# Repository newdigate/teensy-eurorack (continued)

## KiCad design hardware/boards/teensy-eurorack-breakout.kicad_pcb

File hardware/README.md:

# schematics, printed circuit boards, and panels
* schematic and circuit board files for both boards [here](boards)
* panel designs [here](panel)

# circuits images

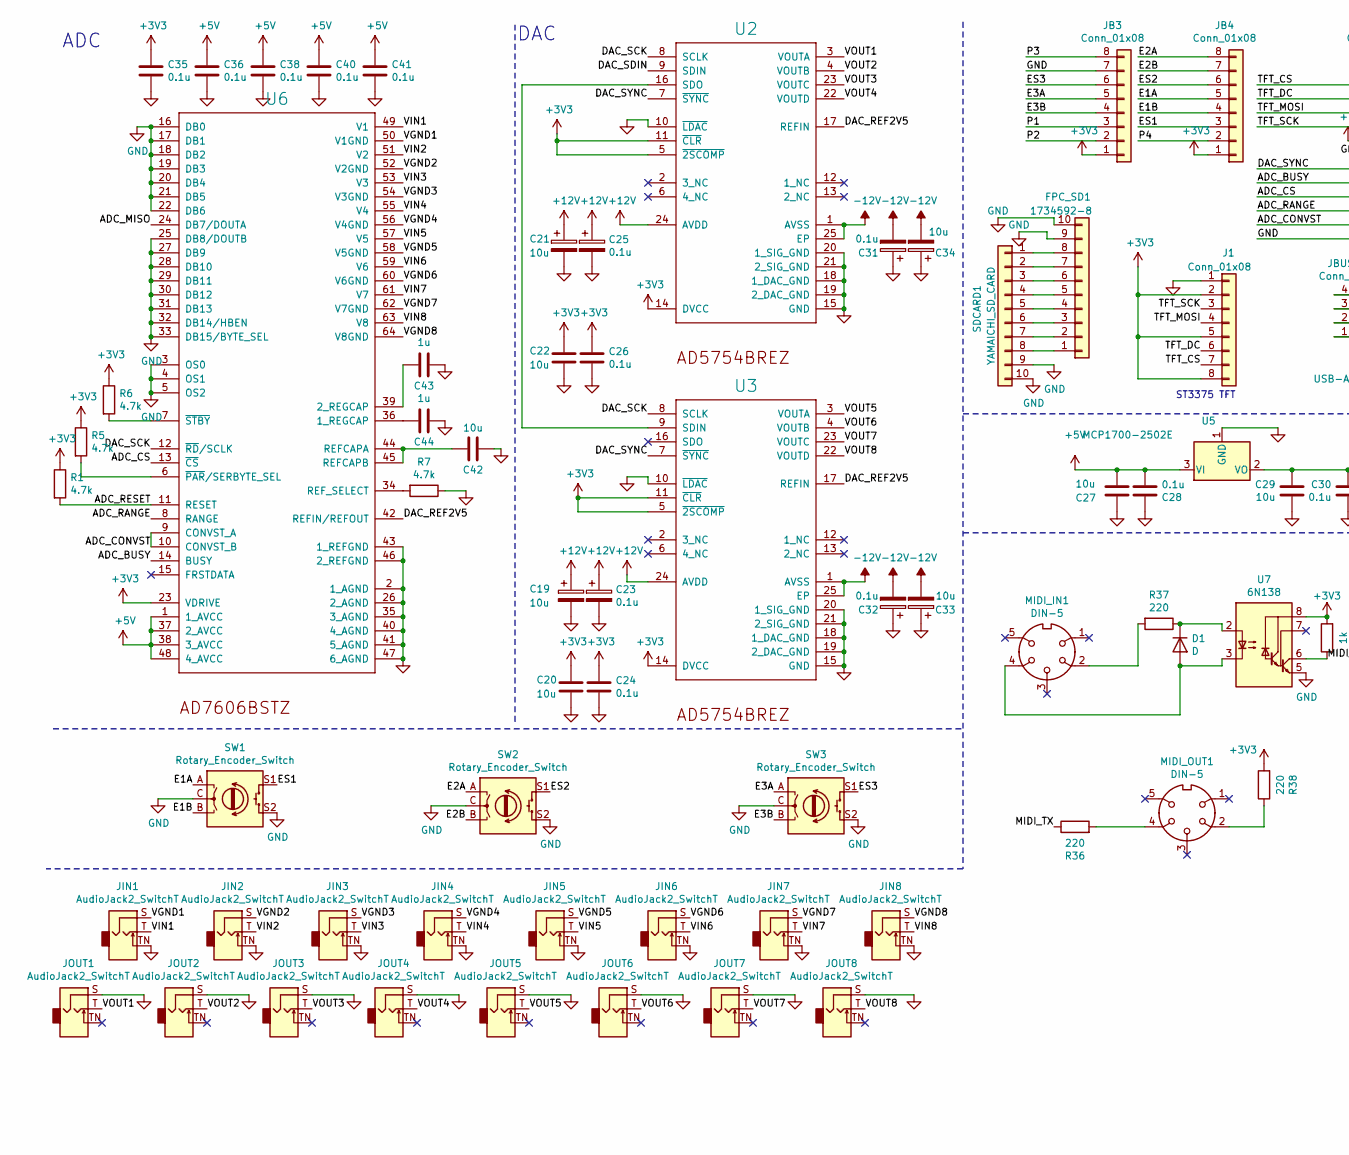
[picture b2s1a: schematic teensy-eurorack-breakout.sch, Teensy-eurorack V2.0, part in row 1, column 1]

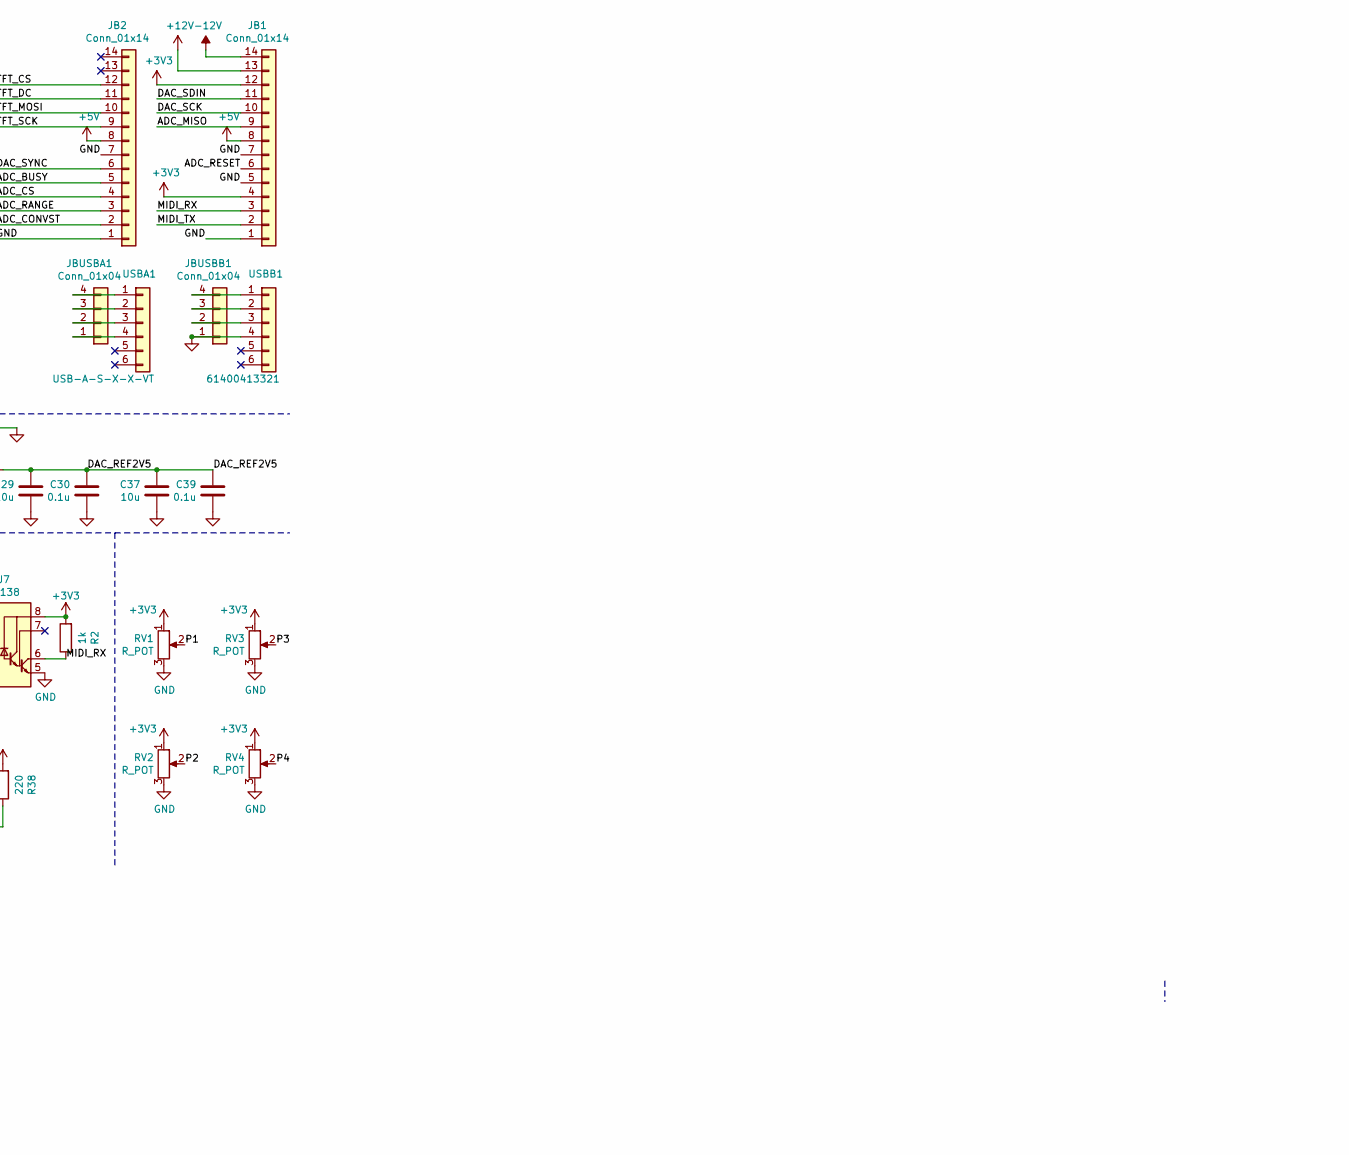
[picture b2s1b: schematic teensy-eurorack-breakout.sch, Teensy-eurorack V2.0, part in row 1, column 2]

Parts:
C19, C21, C33, C34: 10u; CP_Radial_D5.0mm_P2.00mm
C20, C22, C27, C29, C37, C42: 10u; C_0805_2012Metric
C23, C25, C31, C32: 0.1u; CP_Radial_D5.0mm_P2.00mm
C24, C26, C28, C30, C35, C36, C38, C39, C40, C41: 0.1u; C_0805_2012Metric
C43, C44: 1u; C_0805_2012Metric
D1: D; D_0805_2012Metric
FPC_SD1: 1734592-8; HFW8R-1STE1LF
J1: Conn_01x08; ST7735
JB1, JB2: Conn_01x14; PinSocket_1x14_P2.54mm_Vertical
JB3, JB4: Conn_01x08; PinSocket_1x08_P2.54mm_Vertical
JBUSBA1: Conn_01x04; PinSocket_1x04_P2.54mm_Vertical
JBUSBB1: Conn_01x04; PinSocket_1x04_P2.54mm_Vertical
JIN1, JIN2, JIN3, JIN4, JIN5, JIN6, JIN7, JIN8: AudioJack2_SwitchT; WQP-PJ301M-12_JACK
JOUT1, JOUT2, JOUT3, JOUT4, JOUT5, JOUT6, JOUT7, JOUT8: AudioJack2_SwitchT; WQP-PJ301M-12_JACK
MIDI_IN1: DIN-5; OG-MIDI_SD-50BV
MIDI_OUT1: DIN-5; OG-MIDI_SD-50BV
R1, R5, R6, R7: 4.7k; R_0805_2012Metric
R2: 1k; R_0805_2012Metric
R36, R37, R38: 220; R_0805_2012Metric
RV1, RV2, RV3, RV4: R_POT; 9MM_SNAP-IN_POT
SDCARD1: YAMAICHI_SD_CARD; YAMAICHI_MICROSD_VERTICAL
SW1, SW2, SW3: Rotary_Encoder_Switch; RotaryEncoder_Alps_EC12E-Switch_Vertical_H20mm_CircularMoun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
U2, U3: AD5754BREZ; HTSSOP-24-1EP_4.4x7.8mm_P0.65mm_EP3.2x5mm
U5: MCP1700-2502E; SOT-23
U6: AD7606BSTZ; LQFP-64_10x10mm_P0.5mm
U7: 6N138; 6N138S
USBA1: USB-A-S-X-X-VT
USBB1: 61400413321; WURTH_ELECTRONICS_61400413321_0

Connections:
+3V3: C20.1, C22.1, C24.1, C26.1, C35.1, J1.2, J1.5, J1.8, JB1.4, JB1.12, JB3.1, JB4.1, R1.1, R2.2, R5.1, R6.1, R38.2, RV1.1, RV2.1, RV3.1, RV4.1, U2.5 (~2SCOMP~), U2.11 (~CLR~), U2.14 (DVCC), U3.5 (~2SCOMP~), U3.11 (~CLR~), U3.14 (DVCC), U6.23 (VDRIVE), U7.8 (VCC)
+5V: C27.2, C28.2, C36.1, C38.1, C40.1, C41.1, JB1.8, JB2.8, U5.3 (VI), U6.1 (1_AVCC), U6.37 (2_AVCC), U6.38 (3_AVCC), U6.48 (4_AVCC)
+12V: C19.1, C21.1, C23.1, C25.1, JB1.13, U2.24 (AVDD), U3.24 (AVDD)
-12V: C31.2, C32.2, C33.2, C34.2, JB1.14, U2.1 (AVSS), U2.25 (EP), U3.1 (AVSS), U3.25 (EP)
/ADC_BUSY: JB2.5, U6.14 (BUSY)
/ADC_CONVST: JB2.2, U6.9 (CONVST_A), U6.10 (CONVST_B)
/ADC_CS: JB2.4, U6.13 (~CS~)
/ADC_MISO: JB1.9, U6.24 (DB7/DOUTA)
/ADC_RANGE: JB2.3, U6.8 (RANGE)
/ADC_RESET: JB1.6, R1.2, U6.11 (RESET)
/DAC_REF2V5: C29.1, C30.1, C37.1, C39.1, U2.17 (REFIN), U3.17 (REFIN), U5.2 (VO), U6.42 (REFIN/REFOUT)
/DAC_SCK: JB1.10, U2.8 (SCLK), U3.8 (SCLK), U6.12 (~RD~/SCLK)
/DAC_SDIN: JB1.11, U2.9 (SDIN)
/DAC_SYNC: JB2.6, U2.7 (~SYNC~), U3.7 (~SYNC~)
/E1A: JB4.5, SW1.A
/E1B: JB4.4, SW1.B
/E2A: JB4.8, SW2.A
/E2B: JB4.7, SW2.B
/E3A: JB3.5, SW3.A
/E3B: JB3.4, SW3.B
/ES1: JB4.3, SW1.S1
/ES2: JB4.6, SW2.S1
/ES3: JB3.6, SW3.S1
/MIDI_RX: JB1.3, R2.1, U7.6 (VO2)
/MIDI_TX: JB1.2, R36.1
/P1: JB3.3, RV1.2
/P2: JB3.2, RV2.2
/P3: JB3.8, RV3.2
/P4: JB4.2, RV4.2
/TFT_CS: J1.7, JB2.12
/TFT_DC: J1.6, JB2.11
/TFT_MOSI: J1.4, JB2.10
/TFT_SCK: J1.3, JB2.9
/VGND1: JIN1.S, U6.50 (V1GND)
/VGND2: JIN2.S, U6.52 (V2GND)
/VGND3: JIN3.S, U6.54 (V3GND)
/VGND4: JIN4.S, U6.56 (V4GND)
/VGND5: JIN5.S, U6.58 (V5GND)
/VGND6: JIN6.S, U6.60 (V6GND)
/VGND7: JIN7.S, U6.62 (V7GND)
/VGND8: JIN8.S, U6.64 (V8GND)
/VIN1: JIN1.T, U6.49 (V1)
/VIN2: JIN2.T, U6.51 (V2)
/VIN3: JIN3.T, U6.53 (V3)
/VIN4: JIN4.T, U6.55 (V4)
/VIN5: JIN5.T, U6.57 (V5)
/VIN6: JIN6.T, U6.59 (V6)
/VIN7: JIN7.T, U6.61 (V7)
/VIN8: JIN8.T, U6.63 (V8)
/VOUT1: JOUT1.T, U2.3 (VOUTA)
/VOUT2: JOUT2.T, U2.4 (VOUTB)
/VOUT3: JOUT3.T, U2.23 (VOUTC)
/VOUT4: JOUT4.T, U2.22 (VOUTD)
/VOUT5: JOUT5.T, U3.3 (VOUTA)
/VOUT6: JOUT6.T, U3.4 (VOUTB)
/VOUT7: JOUT7.T, U3.23 (VOUTC)
/VOUT8: JOUT8.T, U3.22 (VOUTD)
GND: C19.2, C20.2, C21.2, C22.2, C23.2, C24.2, C25.2, C26.2, C27.1, C28.1, C29.2, C30.2, C31.1, C32.1, C33.1, C34.1, C35.2, C36.2, C37.2, C38.2, C39.2, C40.2, C41.2, C42.1, C43.1, C44.1, FPC_SD1.9, FPC_SD1.10, J1.1, JB1.1, JB1.5, JB1.7, JB2.1, JB2.7, JB3.7, JBUSBB1.1, JIN1.TN, JIN2.TN, JIN3.TN, JIN4.TN, JIN5.TN, JIN6.TN, JIN7.TN, JIN8.TN, JOUT1.S, JOUT2.S, JOUT3.S, JOUT4.S, JOUT5.S, JOUT6.S, JOUT7.S, JOUT8.S, R7.1, RV1.3, RV2.3, RV3.3, RV4.3, SDCARD1.9, SDCARD1.10, SW1.C, SW1.S2, SW2.C, SW2.S2, SW3.C, SW3.S2, U2.10 (~LDAC~), U2.15 (GND), U2.18 (1_DAC_GND), U2.19 (2_DAC_GND), U2.20 (1_SIG_GND), U2.21 (2_SIG_GND), U3.10 (~LDAC~), U3.15 (GND), U3.18 (1_DAC_GND), U3.19 (2_DAC_GND), U3.20 (1_SIG_GND), U3.21 (2_SIG_GND), U5.1 (GND), U6.2 (1_AGND), U6.3 (OS0), U6.4 (OS1), U6.5 (OS2), U6.16 (DB0), U6.17 (DB1), U6.18 (DB2), U6.19 (DB3), U6.20 (DB4), U6.21 (DB5), U6.22 (DB6), U6.25 (DB8/DOUTB), U6.26 (2_AGND), U6.27 (DB9), U6.28 (DB10), U6.29 (DB11), U6.30 (DB12), U6.31 (DB13), U6.32 (DB14/HBEN), U6.33 (DB15/BYTE_SEL), U6.35 (3_AGND), U6.40 (4_AGND), U6.41 (5_AGND), U6.43 (1_REFGND), U6.46 (2_REFGND), U6.47 (6_AGND), U7.5 (GND), USBB1.4
unnamed: C42.2, U6.44 (REFCAPA), U6.45 (REFCAPB)
unnamed: C43.2, U6.39 (2_REGCAP)
unnamed: C44.2, U6.36 (1_REGCAP)
unnamed: D1.1 (K), R37.1, U7.2 (C1)
unnamed: D1.2 (A), MIDI_IN1.4, U7.3 (C2)
unnamed: FPC_SD1.1, SDCARD1.8
unnamed: FPC_SD1.2, SDCARD1.7
unnamed: FPC_SD1.3, SDCARD1.6
unnamed: FPC_SD1.4, SDCARD1.5
unnamed: FPC_SD1.5, SDCARD1.4
unnamed: FPC_SD1.6, SDCARD1.3
unnamed: FPC_SD1.7, SDCARD1.2
unnamed: FPC_SD1.8, SDCARD1.1
unnamed: JBUSBA1.1, USBA1.4
unnamed: JBUSBA1.2, USBA1.3
unnamed: JBUSBA1.3, USBA1.2
unnamed: JBUSBA1.4, USBA1.1
unnamed: JBUSBB1.2, USBB1.3
unnamed: JBUSBB1.3, USBB1.2
unnamed: JBUSBB1.4, USBB1.1
unnamed: MIDI_IN1.2, R37.2
unnamed: MIDI_OUT1.2, R38.1
unnamed: MIDI_OUT1.4, R36.2
unnamed: R5.2, U6.6 (~PAR~/SERBYTE_SEL)
unnamed: R6.2, U6.7 (~STBY~)
unnamed: R7.2, U6.34 (REF_SELECT)
unnamed: U2.16 (SDO), U3.9 (SDIN)

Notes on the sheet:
ADC
ST3375 TFT
DAC

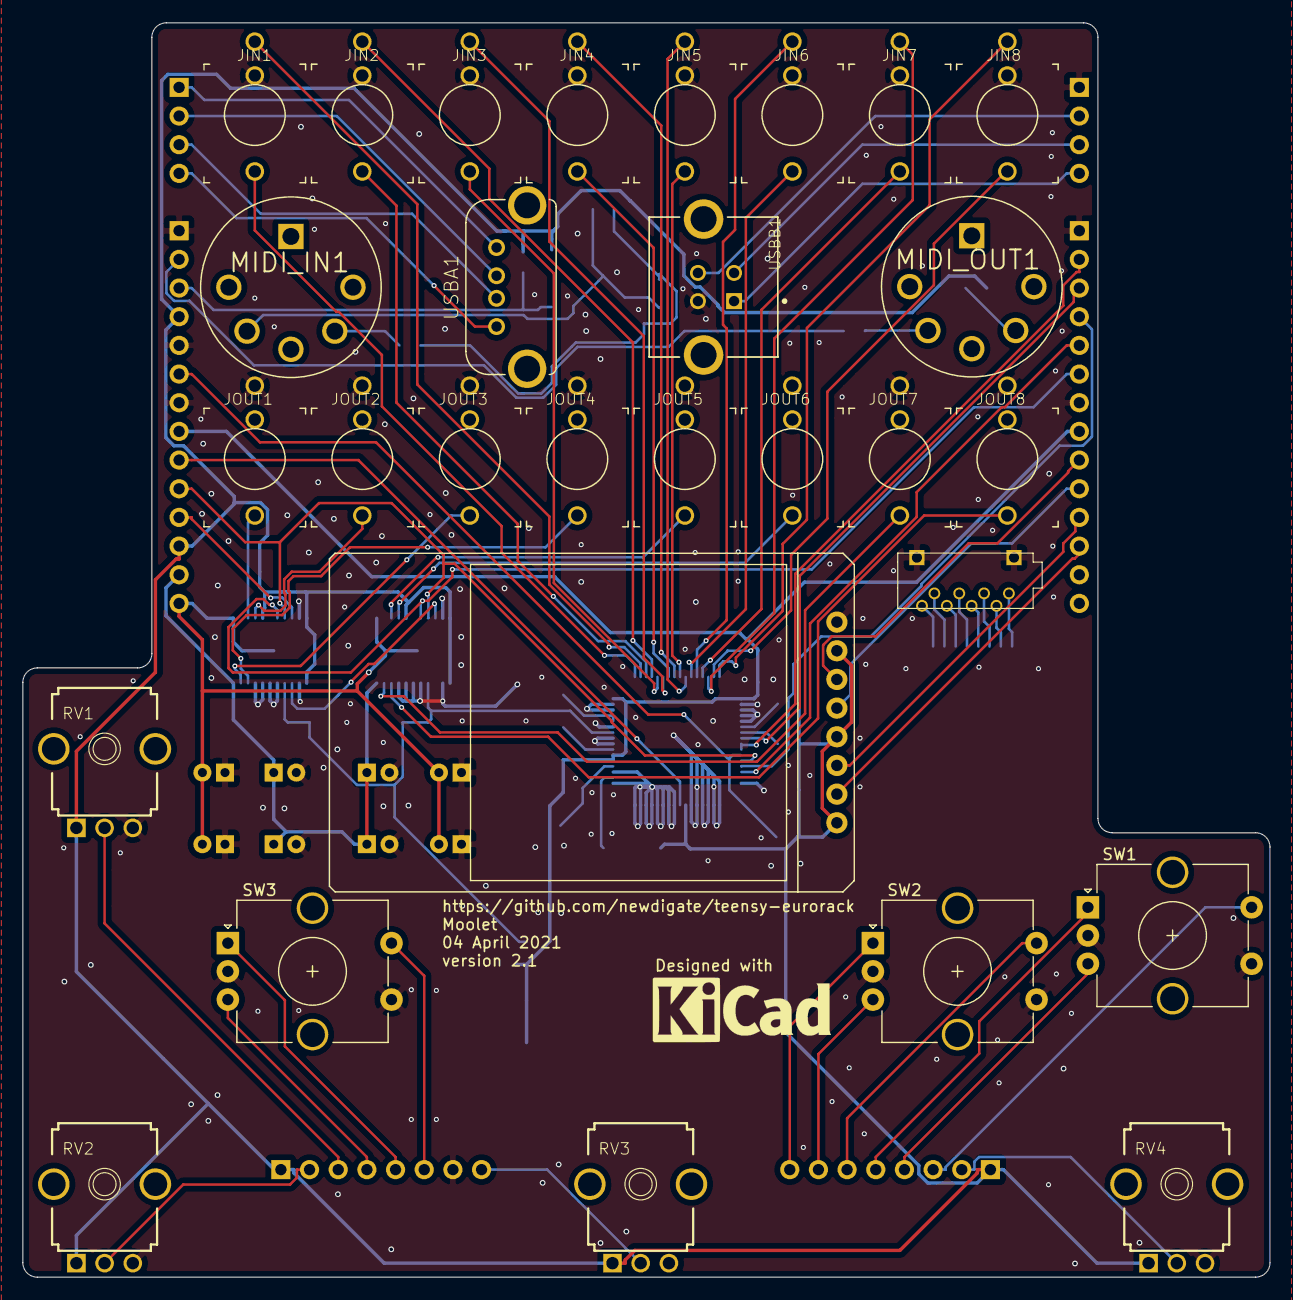
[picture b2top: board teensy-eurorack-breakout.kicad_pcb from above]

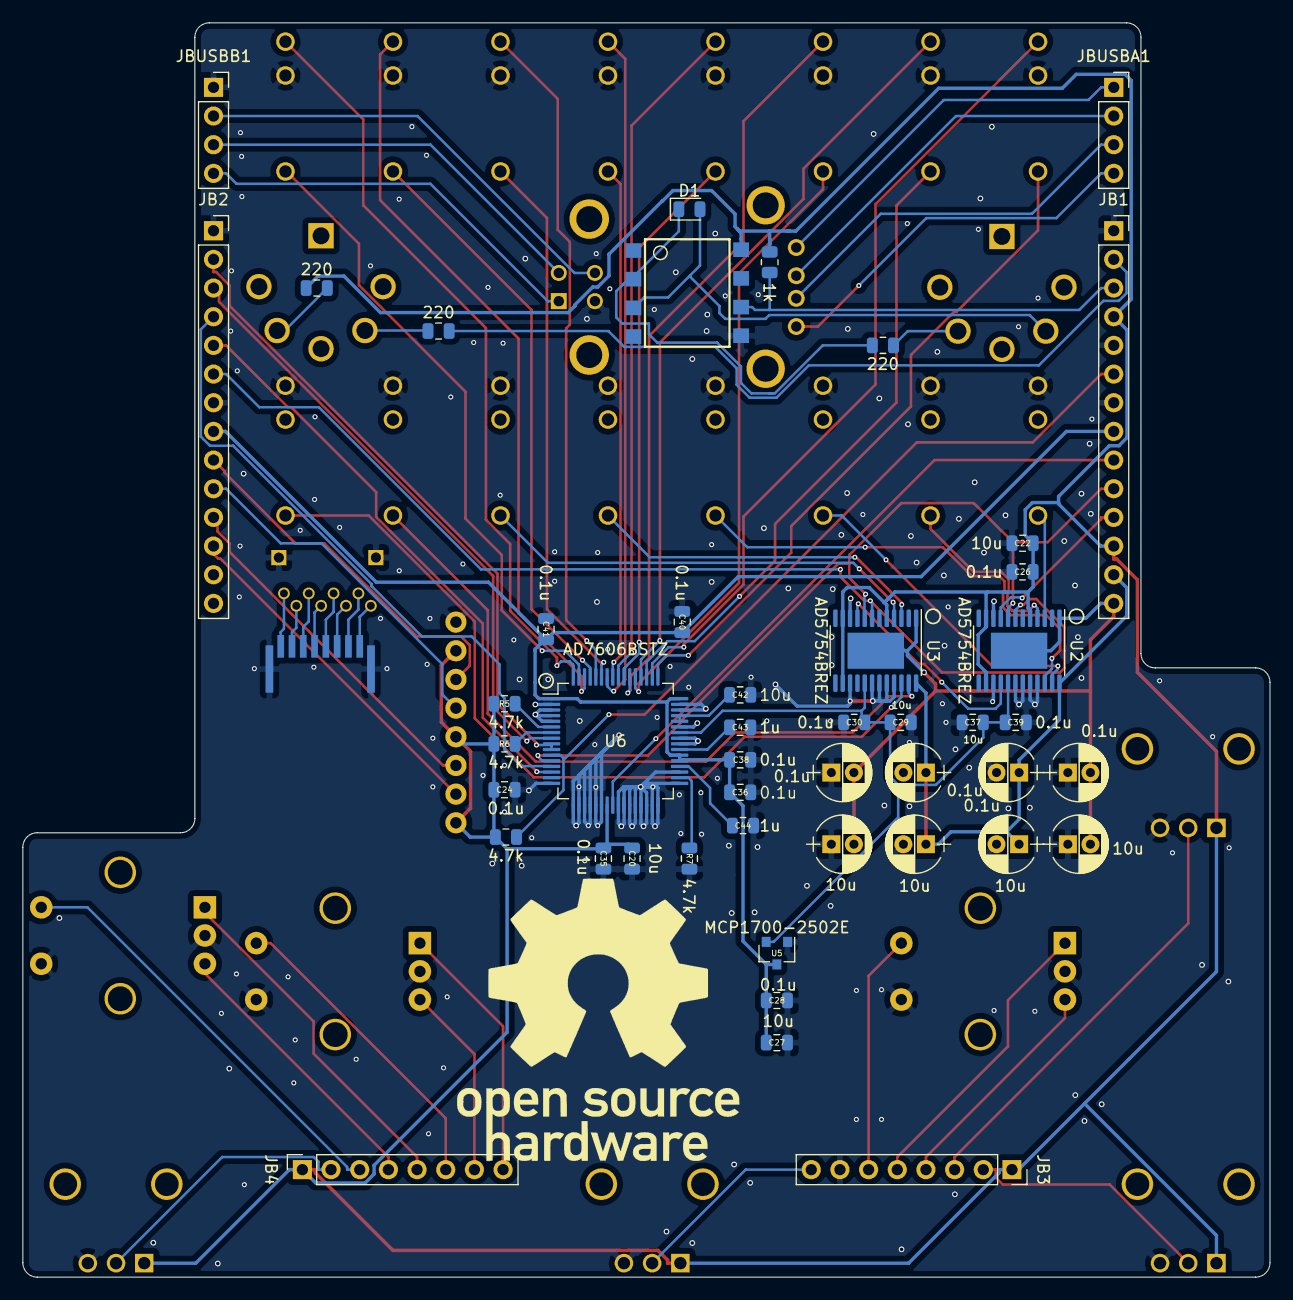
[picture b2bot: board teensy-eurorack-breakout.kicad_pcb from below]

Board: 2 copper layers, 110.5 x 111.1 mm, 76 parts (47 on the bottom side), 85 nets.

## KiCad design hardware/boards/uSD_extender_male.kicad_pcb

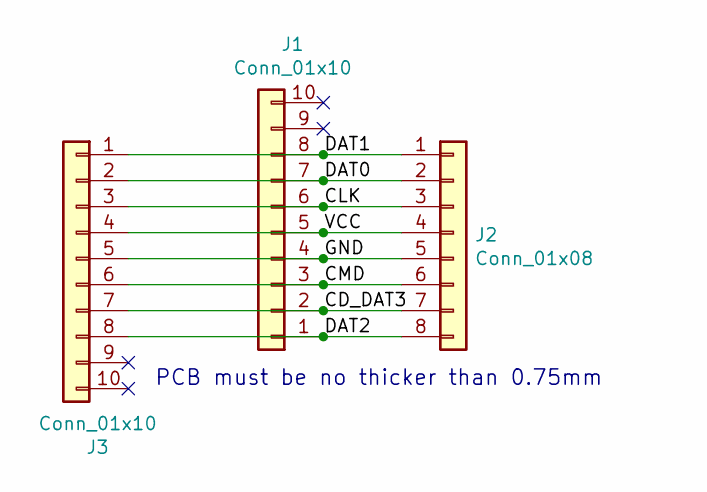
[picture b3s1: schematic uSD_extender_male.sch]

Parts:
J1, J3: Conn_01x10; HFW8R-1STE1LF
J2: Conn_01x08; MICRO-SDCARD

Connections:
/CD_DAT3: J1.2, J2.7, J3.7
/CLK: J1.6, J2.3, J3.3
/CMD: J1.3, J2.6, J3.6
/DAT0: J1.7, J2.2, J3.2
/DAT1: J1.8, J2.1, J3.1
/DAT2: J1.1, J2.8, J3.8
/GND: J1.4, J2.5, J3.5
/VCC: J1.5, J2.4, J3.4

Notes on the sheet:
PCB must be no thicker than 0.75mm

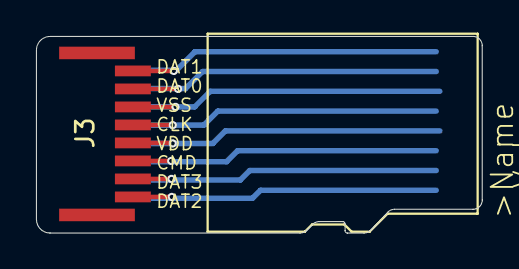
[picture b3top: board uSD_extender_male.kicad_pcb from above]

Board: 2 copper layers, 24.8 x 10.9 mm, 3 parts (0 on the bottom side), 8 nets.

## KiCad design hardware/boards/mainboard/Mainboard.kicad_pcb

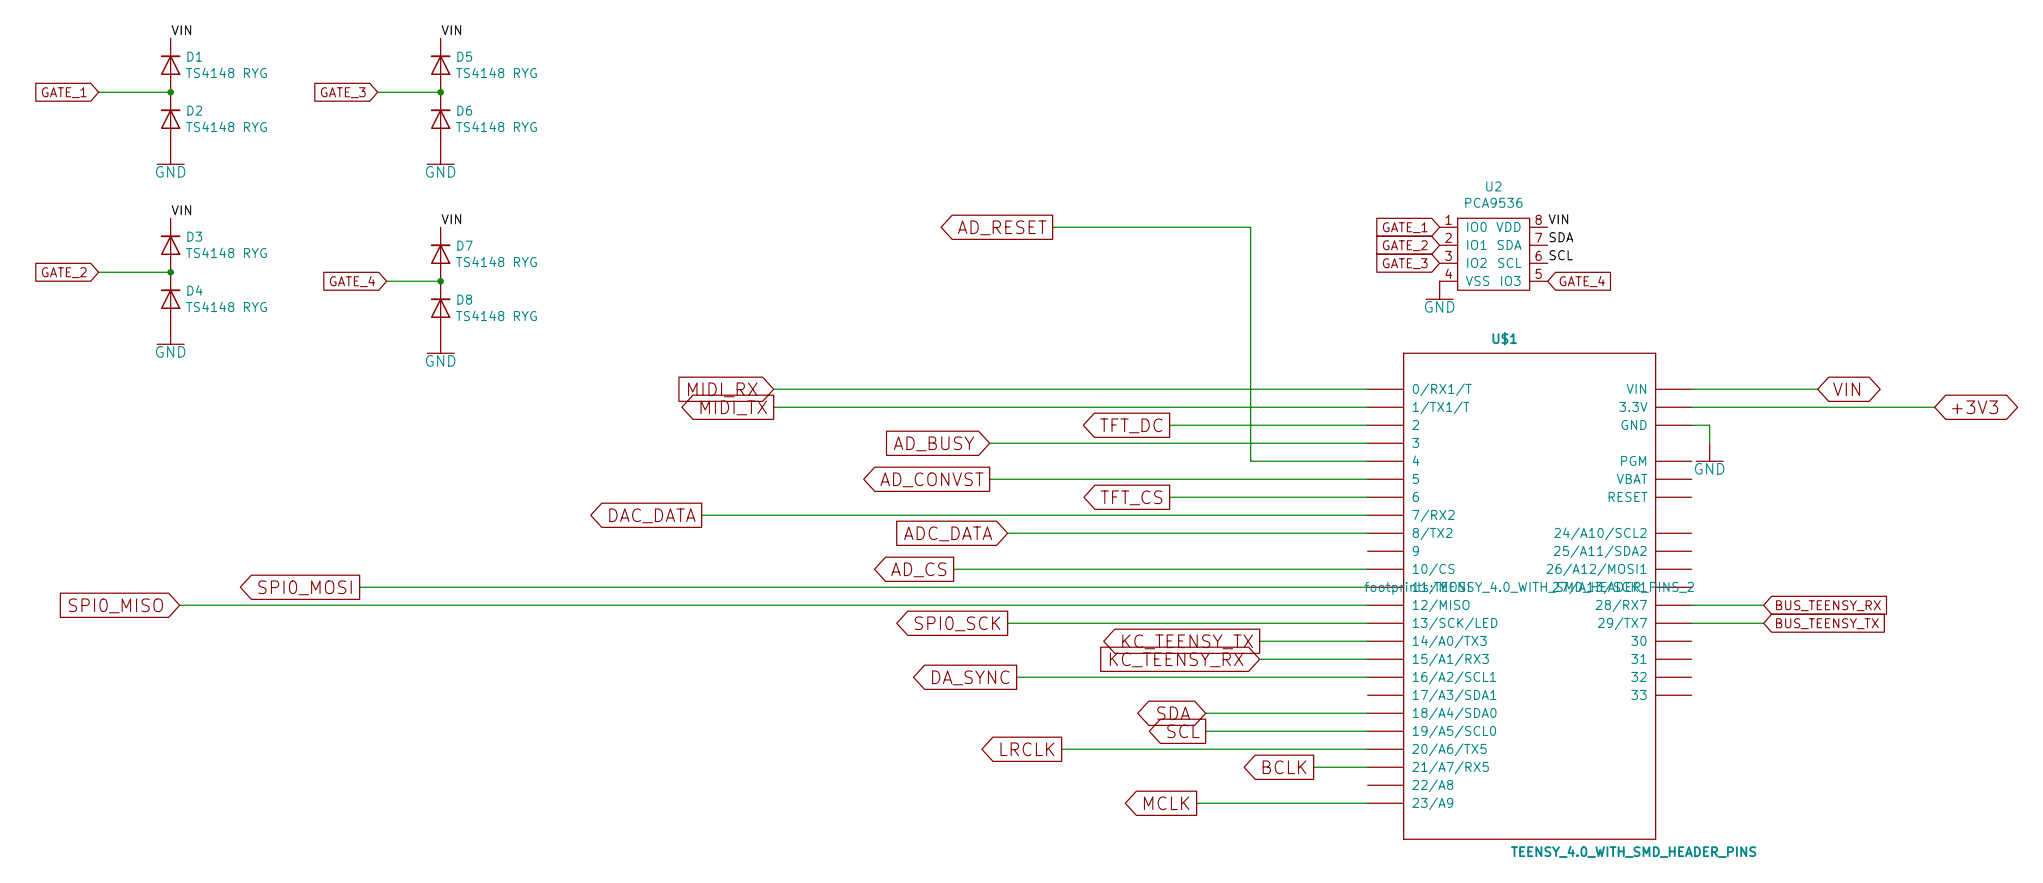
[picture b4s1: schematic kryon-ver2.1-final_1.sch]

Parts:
D1, D2, D3, D4, D5, D6, D7, D8: TS4148 RYG; D_0805_2012Metric
U2: PCA9536; TSSOP-8_3x3mm_P0.65mm
U$1: TEENSY_4.0_WITH_SMD_HEADER_PINS; TEENSY_4.0_WITH_SMD_HEADER_PINS_2

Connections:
+3V3: U$1.3.3V, U$1.3.3V1 (3.3V); also elsewhere on the board
ADC_DATA: U$1.8 (8/TX2); also elsewhere on the board
AD_BUSY: U$1.3; also elsewhere on the board
AD_CONVST: U$1.5; also elsewhere on the board
AD_CS: U$1.10 (10/CS); also elsewhere on the board
AD_RESET: U$1.4; also elsewhere on the board
BCLK: U$1.21/A7 (21/A7/RX5); also elsewhere on the board
BUS_TEENSY_RX: U$1.28 (28/RX7); also elsewhere on the board
BUS_TEENSY_TX: U$1.29 (29/TX7); also elsewhere on the board
DAC_DATA: U$1.7 (7/RX2); also elsewhere on the board
DA_SYNC: U$1.16/A2 (16/A2/SCL1); also elsewhere on the board
GATE_1: D1.2 (A), D2.1 (K), U2.1 (IO0); also elsewhere on the board
GATE_2: D3.2 (A), D4.1 (K), U2.2 (IO1); also elsewhere on the board
GATE_3: D5.2 (A), D6.1 (K), U2.3 (IO2); also elsewhere on the board
GATE_4: D7.2 (A), D8.1 (K), U2.5 (IO3); also elsewhere on the board
GND: D2.2 (A), D4.2 (A), D6.2 (A), D8.2 (A), U2.4 (VSS), U$1.GND, U$1.GND1 (GND), U$1.GND2 (GND); also elsewhere on the board
KC_TEENSY_RX: U$1.15/A1 (15/A1/RX3); also elsewhere on the board
KC_TEENSY_TX: U$1.14/A0 (14/A0/TX3); also elsewhere on the board
LRCLK: U$1.20/A6 (20/A6/TX5); also elsewhere on the board
MCLK: U$1.23/A9; also elsewhere on the board
MIDI_RX: U$1.0 (0/RX1/T); also elsewhere on the board
MIDI_TX: U$1.1 (1/TX1/T); also elsewhere on the board
SCL: U2.6 (SCL), U$1.19/A5 (19/A5/SCL0); also elsewhere on the board
SDA: U2.7 (SDA), U$1.18/A4 (18/A4/SDA0); also elsewhere on the board
SPI0_MISO: U$1.12 (12/MISO); also elsewhere on the board
SPI0_MOSI: U$1.11 (11/MOSI); also elsewhere on the board
SPI0_SCK: U$1.13 (13/SCK/LED); also elsewhere on the board
TFT_CS: U$1.6; also elsewhere on the board
TFT_DC: U$1.2; also elsewhere on the board
VIN: D1.1 (K), D3.1 (K), D5.1 (K), D7.1 (K), U2.8 (VDD), U$1.VIN; also elsewhere on the board

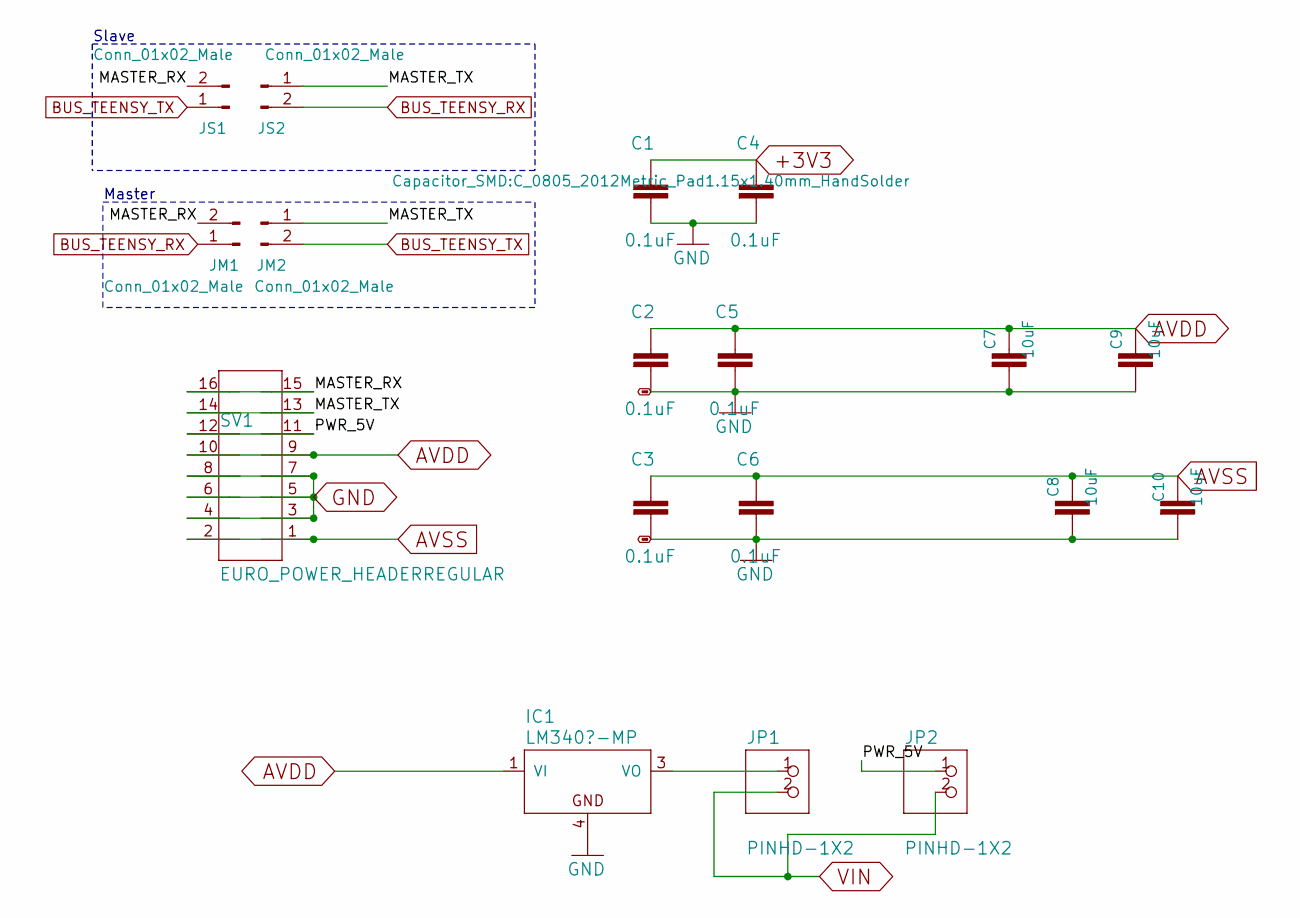
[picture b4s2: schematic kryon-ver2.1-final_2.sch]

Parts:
C1, C2, C3, C4, C5, C6: 0.1uF; C_0805_2012Metric_Pad1.15x1.40mm_HandSolder
C7, C8, C9, C10: 10uF; C_0805_2012Metric_Pad1.15x1.40mm_HandSolder
IC1: LM340?-MP; SOT-223
JM1, JM2: Conn_01x02_Male; PinHeader_1x02_P2.54mm_Vertical
JP1, JP2: PINHD-1X2; 1X02
JS1, JS2: Conn_01x02_Male; PinHeader_1x02_P2.54mm_Vertical
SV1: EURO_POWER_HEADERREGULAR; PinHeader_2x08_P2.54mm_Vertical

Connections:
+3V3: C1.1, C4.1; also elsewhere on the board
/Power and bypass caps/MASTER_RX: JM1.2, JS1.2, SV1.15, SV1.16
/Power and bypass caps/MASTER_TX: JM2.1, JS2.1, SV1.13, SV1.14
/Power and bypass caps/PWR_5V: JP2.1, SV1.11, SV1.12
AVDD: C2.1, C5.1, C7.1, C9.1, IC1.1 (VI), SV1.9, SV1.10; also elsewhere on the board
AVSS: C3.1, C6.1, C8.1, C10.1, SV1.1, SV1.2; also elsewhere on the board
BUS_TEENSY_RX: JM1.1, JS2.2; also elsewhere on the board
BUS_TEENSY_TX: JM2.2, JS1.1; also elsewhere on the board
GND: C1.2, C2.2, C3.2, C4.2, C5.2, C6.2, C7.2, C8.2, C9.2, C10.2, IC1.4 (GND), SV1.3, SV1.4, SV1.5, SV1.6, SV1.7, SV1.8; also elsewhere on the board
unnamed: IC1.3 (VO), JP1.1
VIN: JP1.2, JP2.2; also elsewhere on the board

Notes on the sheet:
Slave
Master

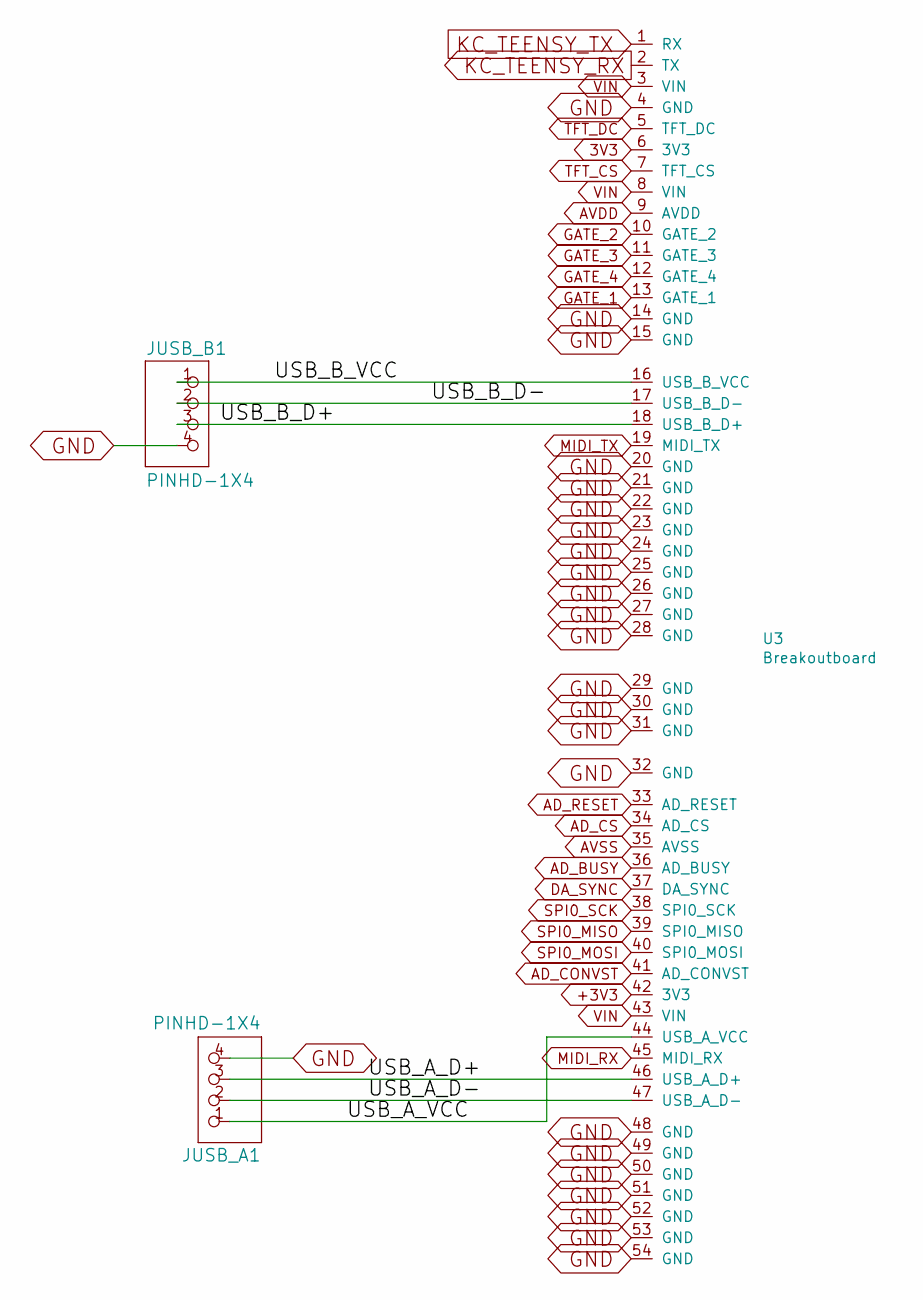
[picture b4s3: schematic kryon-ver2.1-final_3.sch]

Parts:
JUSB_A1: PINHD-1X4; 1X04
JUSB_B1: PINHD-1X4; 1X04
U3: Breakoutboard

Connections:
3V3: U3.6 (3V3); also elsewhere on the board
+3V3: U3.42 (3V3); also elsewhere on the board
/daughter board connectors/USB_A_D+: JUSB_A1.3, U3.46 (USB_A_D+)
/daughter board connectors/USB_A_D-: JUSB_A1.2, U3.47 (USB_A_D-)
/daughter board connectors/USB_A_VCC: JUSB_A1.1, U3.44 (USB_A_VCC)
/daughter board connectors/USB_B_D+: JUSB_B1.3, U3.18 (USB_B_D+)
/daughter board connectors/USB_B_D-: JUSB_B1.2, U3.17 (USB_B_D-)
/daughter board connectors/USB_B_VCC: JUSB_B1.1, U3.16 (USB_B_VCC)
AD_BUSY: U3.36 (AD_BUSY); also elsewhere on the board
AD_CONVST: U3.41 (AD_CONVST); also elsewhere on the board
AD_CS: U3.34 (AD_CS); also elsewhere on the board
AD_RESET: U3.33 (AD_RESET); also elsewhere on the board
AVDD: U3.9 (AVDD); also elsewhere on the board
AVSS: U3.35 (AVSS); also elsewhere on the board
DA_SYNC: U3.37 (DA_SYNC); also elsewhere on the board
GATE_1: U3.13 (GATE_1); also elsewhere on the board
GATE_2: U3.10 (GATE_2); also elsewhere on the board
GATE_3: U3.11 (GATE_3); also elsewhere on the board
GATE_4: U3.12 (GATE_4); also elsewhere on the board
GND: JUSB_A1.4, JUSB_B1.4, U3.4 (GND), U3.14 (GND), U3.15 (GND), U3.20 (GND), U3.21 (GND), U3.22 (GND), U3.23 (GND), U3.24 (GND), U3.25 (GND), U3.26 (GND), U3.27 (GND), U3.28 (GND), U3.29 (GND), U3.30 (GND), U3.31 (GND), U3.32 (GND), U3.48 (GND), U3.49 (GND), U3.50 (GND), U3.51 (GND), U3.52 (GND), U3.53 (GND), U3.54 (GND); also elsewhere on the board
KC_TEENSY_RX: U3.2 (TX); also elsewhere on the board
KC_TEENSY_TX: U3.1 (RX); also elsewhere on the board
MIDI_RX: U3.45 (MIDI_RX); also elsewhere on the board
MIDI_TX: U3.19 (MIDI_TX); also elsewhere on the board
SPI0_MISO: U3.39 (SPI0_MISO); also elsewhere on the board
SPI0_MOSI: U3.40 (SPI0_MOSI); also elsewhere on the board
SPI0_SCK: U3.38 (SPI0_SCK); also elsewhere on the board
TFT_CS: U3.7 (TFT_CS); also elsewhere on the board
TFT_DC: U3.5 (TFT_DC); also elsewhere on the board
VIN: U3.3 (VIN), U3.8 (VIN), U3.43 (VIN); also elsewhere on the board
